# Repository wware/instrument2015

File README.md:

<!--
pip install markdown
python -m markdown README.md > README.html
-->

The Tooba is an electronic musical instrument built into a piece of PVC tubing (hence the name). It borrows principles from the Moog-style analog music synthesizers of past decades.

Way back when, one of my friends in high school was a guy named [Dave Wilson](http://www.matrixsynth.com/2010/08/rip-david-hillel-wilson-curator-of-new.html) whose father got him into 1970s-era Moog-style analog electronic music synthesizers. Dave created a museum of historical synthesizers in his home in Nashua, New Hampshire. Throughout our high school and college years, we exchanged ideas and circuits and bits of lore for various synthesizer hacks.

Music synthesizers of that era were actually special-purpose [analog computers](https://en.wikipedia.org/wiki/Analog_computer), performing arithmetic operations with [integrators, summers, and other such circuits](https://courses.engr.illinois.edu/ece486/labs/lab1/analog_computer_manual.pdf). These computations can be performed digitally by a microprocessor or special-purpose digital circuit (e.g. FPGA). So Dave and I both at various points and in various contexts wrote code to do that.

Sound generation in the Tooba (and keyboard scanning and voice assignment) is done in [C++](https://github.com/wware/instrument2015/blob/master/nextstage/teensy/teensy.ino) running on a 32-bit ARM microcontroller.

Newer stuff, November 2015
----

People have expressed interest in purchasing Toobas, so I have been planning some improvements.
* An internal [sound transducer](https://www.adafruit.com/products/1784) driven by a [D-class audio amp](http://www.ti.com/lit/ds/slos527a/slos527a.pdf).
* This requires a 12-volt battery, so I need a [5-volt regulator](https://www.adafruit.com/products/1385).
* A volume control, and jacks for both 1/4" (guitar amps) and 3.5mm (ear buds, computer speakers).
* Cleaned-up mechanics, no giant cabinet hinges.
* A lower-temperature process for soldering keys, so that the copper is not discolored. Producing keys is easier and quicker.

I've used this and another project to start planning 3D constructions in OpenSCAD. This can go farther. Write modules that produce OpenSCAD models for [inclusion in the whole](https://en.wikibooks.org/wiki/OpenSCAD_User_Manual/Include_Statement) but are also a [modular BOM](https://en.wikipedia.org/wiki/Bill_of_materials). Modules for 3D-printable blocks should be able to produce STL files and specify what materials are acceptable. Modules for parts from Home Depot or Adafruit or Digikey should include prices, SKUs, part numbers, etc.

Status, plans, etc
----

The first PVC prototype, the one shown at Providence on Aug 8th 2015, did all sound generation in the interrupt handler. More recently, the interrupt handler only transfers audio samples from a queue to the microcontroller's on-chip 12-bit DAC, and sound generation occurs in the loop() function.

* Doxygen stuff is now [online](http://wware.github.io/instrument2015/).
* Removing sound generation from the interrupt handler and moving it into the main loop solved a LOT of problems, and now I can run the interrupt at 40 kHz. But I am still hearing some aliasing, so I'll need a lowpass filter after the DAC. Use this [rail-to-rail op amp](http://www.digikey.com/product-detail/en/LT1677CN8%23PBF/LT1677CN8%23PBF-ND/962980).
* ADSR and other slow-moving things should perform real calculations at only around 50 Hz, not 40 or 50 kHz. In between calculations they should use linear interpolation. Four billion divided by 50K is 80K, so it’s fine to use 16 fraction bits to interpolate. This will significantly speed things up.
* Never copy or move blocks of data. Move pointers instead. The persistence data for a voice should live in one place and never move.
* The next step right now is to take the code in the Voice class and split it into VCO, VCA and ADSR classes. Then add a Noise class, a Scaler class, a Summer class, and a VCF class. The audio outputs of all these should be 24-bit signed integers in the range from -0x80_0000 to 0x7F_FFFF. Use asserts to make sure they never go outside that range.
* Set up a [monkey test framework](https://en.wikipedia.org/wiki/Monkey_test) that virtually pounds on the keyboard, and detects overflows, underruns, etc.
  * A [SWIG wrapper](http://swig.org/) will be very helpful with this.

Teensy 3.1 info
----

* [The Freescale Semiconductor web page](http://www.freescale.com/webapp/sps/site/prod_summary.jsp?code=K20_50) for the MK20DX256VLH7 processor used in the Teensy 3.1.
* [The datasheet](https://www.pjrc.com/teensy/K20P64M72SF1RM.pdf) that talks about GPIO programming starting on page 1331.
* [The Teensy 3.1 schematic](https://www.pjrc.com/teensy/schematic.html). PTB17 is the GPIO that I want to read. The Port B input register is at 0x400FF050. There is no MMU so no need for any mmap craziness.
* [Here](https://forum.pjrc.com/threads/25317-Assembly-coding-for-Teensy3-1) is a great discussion of embedding assembly in C code. Also see http://www.ethernut.de/en/documents/arm-inline-asm.html.
* [A C header file](http://www.keil.com/dd/docs/arm/freescale/kinetis/mk20d7.h) for registers in the MK20DX.
* [Some nice info](http://www.peter-cockerell.net/aalp/html/frames.html) on ARM assembly language.

Earlier prototype
----

I want to read the GPIO in assembly to accurately measure the period of the oscillator. This code ran on the June prototype and measured the capacitance of the touch sensitive keyboard. The capacitance was used in the RC time constant of a free-running oscillator and the idea here is to get a measurement roughly proportional to the period.

1. Set counter to zero.
2. If input is LOW, go to step 7.
3. Wait for a falling edge. Proceed when input is LOW.
4. Increment counter while waiting for rising edge. Proceed when input is HIGH.
5. Increment counter while waiting for falling edge. Proceed when input is LOW.
6. Go to step 10.
7. Wait for a rising edge. Proceed when input is HIGH.
8. Increment counter while waiting for falling edge. Proceed when input is LOW.
9. Increment counter while waiting for rising edge. Proceed when input is HIGH.
10. Return counter.

So that piece is assembly, and then in C you choose a touch contact and call that function. That should ensure that you read the keyboard about as fast as it can be read. The code for this is buried in [the sandbox directory](https://github.com/wware/instrument2015/blob/master/sandbox/prototype1/prototype1.ino#L7).

~~~
static int measurePeriod(void)
{
    // Step 1, set up registers
    int count = 0, x = 0, mask = 1 << 17, addr = 0x400ff050;
#   define READ_INPUT  "ldr %1, [%3]\n"     "ands %1, %1, %2\n"
#   define INC_COUNT   "add %0, %0, #1\n"
    asm volatile(
        // Step 2, if input is low go to step 7
        READ_INPUT
        "beq step7"                             "\n"
        // Step 3, wait for falling edge
        "step3:"                                "\n"

        ... lots more code ...

        "step10:"                               "\n"
        : "+r" (count), "+r" (x), "+r" (mask), "+r" (addr)
    );
    return count;
}
~~~

This works well in both the [Arduino/Teensy IDE](https://www.pjrc.com/teensy/teensyduino.html) and in the [online ARM C++ compiler](http://assembly.ynh.io/).

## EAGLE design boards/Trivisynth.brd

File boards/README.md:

Printed circuit boards
====

I use Cadsoft Eagle for PCB layout. For these designs you'll need to pick up
some third-party libraries.

* [Teensy 3.0 library](https://forum.pjrc.com/attachment.php?attachmentid=184&d=1358973338)
  - [Discussion of Teensy library](https://www.pjrc.com/teensy/eagle_lib.html)
* [Sparkfun Connector library](https://github.com/sparkfun/SparkFun-Eagle-Libraries)

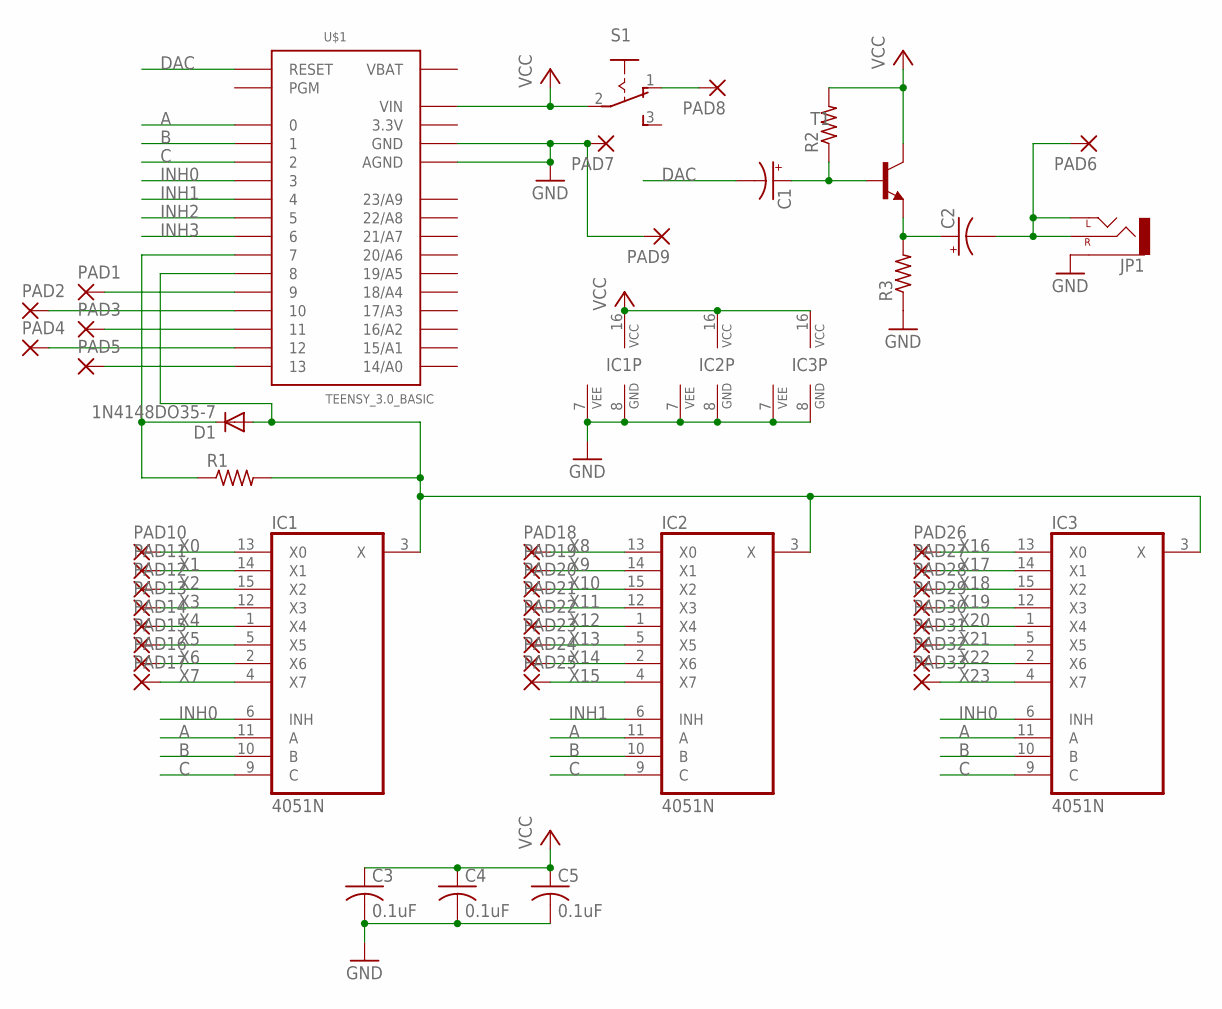
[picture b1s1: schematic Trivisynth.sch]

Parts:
C1, C2: CPOL-USE2-5; E2-5
C3, C4, C5: 0.1uF; C025-025X050
D1: 1N4148DO35-7; DO35-7
IC1, IC2, IC3: 4051N; DIL16
JP1: AUDIO-JACKPTH; AUDIO-JACK
PAD1, PAD2, PAD3, PAD4, PAD5, PAD6, PAD7, PAD8, PAD9, PAD10, PAD11, PAD12, PAD13, PAD14, PAD15, PAD16, PAD17, PAD18, PAD19, PAD20, PAD21, PAD22, PAD23, PAD24, PAD25, PAD26, PAD27, PAD28, PAD29, PAD30, PAD31, PAD32, PAD33: 2,15/1,0
R1, R2, R3: R-US_0207/10; 0207/10
S1: 255SB
T1: -NPN-TO92-EBC; TO92-EBC
U$1: TEENSY_3.0_BASIC

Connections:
3.3V: U$1.3.3V, U$1.3.3V1 (3.3V)
A: IC1.11 (A), IC2.11 (A), IC3.11 (A), U$1.0
B: IC1.10 (B), IC2.10 (B), IC3.10 (B), U$1.1
C: IC1.9 (C), IC2.9 (C), IC3.9 (C), U$1.2
DAC: C1.-, U$1.RESET
GND: C3.2, C4.2, C5.2, IC1.7 (VEE), IC1.8 (GND), IC2.7 (VEE), IC2.8 (GND), IC3.7 (VEE), IC3.8 (GND), JP1.SLEEVE, PAD7.1, PAD9.1, R3.1, U$1.AGND, U$1.GND, U$1.GND1 (GND)
INH0: IC1.6 (INH), IC3.6 (INH), U$1.3
INH1: IC2.6 (INH), U$1.4
INH2: U$1.5
INH3: U$1.6
unnamed: PAD8.1, S1.1 (O)
unnamed: D1.A, IC1.3 (X), IC2.3 (X), IC3.3 (X), R1.2, U$1.8
unnamed: C1.+, R2.1, T1.B
unnamed: C2.+, R3.2, T1.E
unnamed: D1.C, R1.1, U$1.7
unnamed: C2.-, JP1.RING (RIGHT), JP1.TIP (LEFT), PAD6.1
unnamed: PAD1.1, U$1.9
unnamed: PAD2.1, U$1.10
unnamed: PAD3.1, U$1.11
unnamed: PAD4.1, U$1.12
unnamed: PAD5.1, U$1.13
VBAT: U$1.VBAT
VCC: C3.1, C4.1, C5.1, IC1.16 (VCC), IC2.16 (VCC), IC3.16 (VCC), R2.2, S1.2, T1.C, U$1.VIN
X0: IC1.13 (X0), PAD10.1
X1: IC1.14 (X1), PAD11.1
X2: IC1.15 (X2), PAD12.1
X3: IC1.12 (X3), PAD13.1
X4: IC1.1 (X4), PAD14.1
X5: IC1.5 (X5), PAD15.1
X6: IC1.2 (X6), PAD16.1
X7: IC1.4 (X7), PAD17.1
X8: IC2.13 (X0), PAD18.1
X9: IC2.14 (X1), PAD19.1
X10: IC2.15 (X2), PAD20.1
X11: IC2.12 (X3), PAD21.1
X12: IC2.1 (X4), PAD22.1
X13: IC2.5 (X5), PAD23.1
X14: IC2.2 (X6), PAD24.1
X15: IC2.4 (X7), PAD25.1
X16: IC3.13 (X0), PAD26.1
X17: IC3.14 (X1), PAD27.1
X18: IC3.15 (X2), PAD28.1
X19: IC3.12 (X3), PAD29.1
X20: IC3.1 (X4), PAD30.1
X21: IC3.5 (X5), PAD31.1
X22: IC3.2 (X6), PAD32.1
X23: IC3.4 (X7), PAD33.1

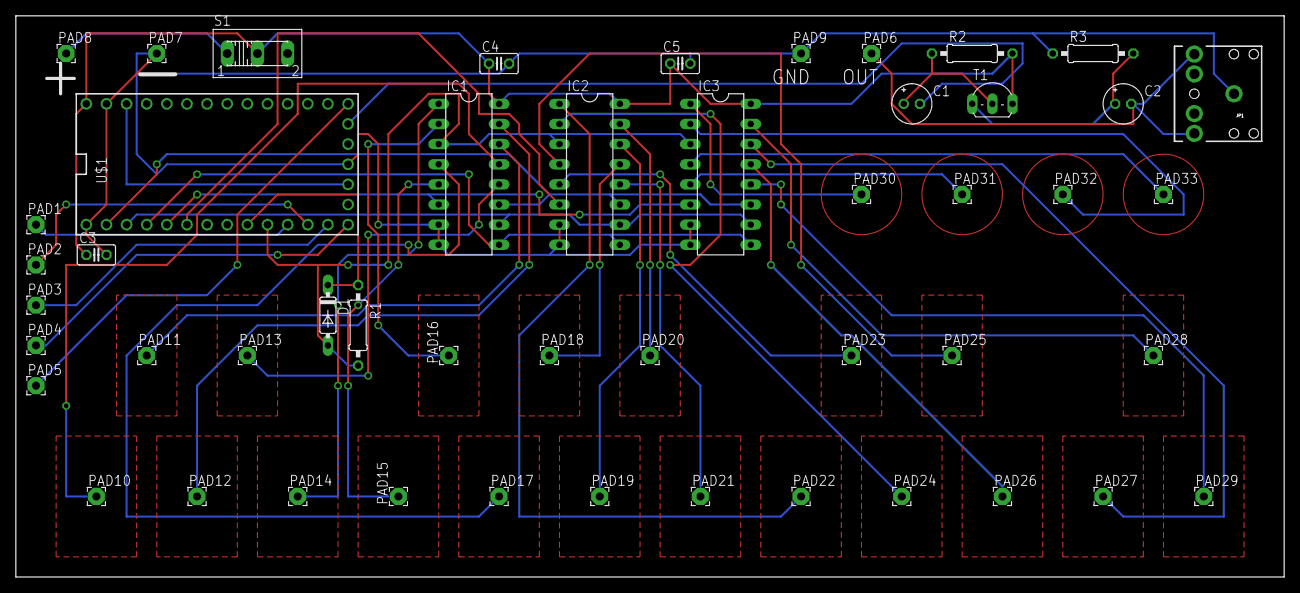
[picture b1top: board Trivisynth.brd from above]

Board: 2 copper layers, 160.0 x 70.8 mm, 49 parts (0 on the bottom side), 44 nets.

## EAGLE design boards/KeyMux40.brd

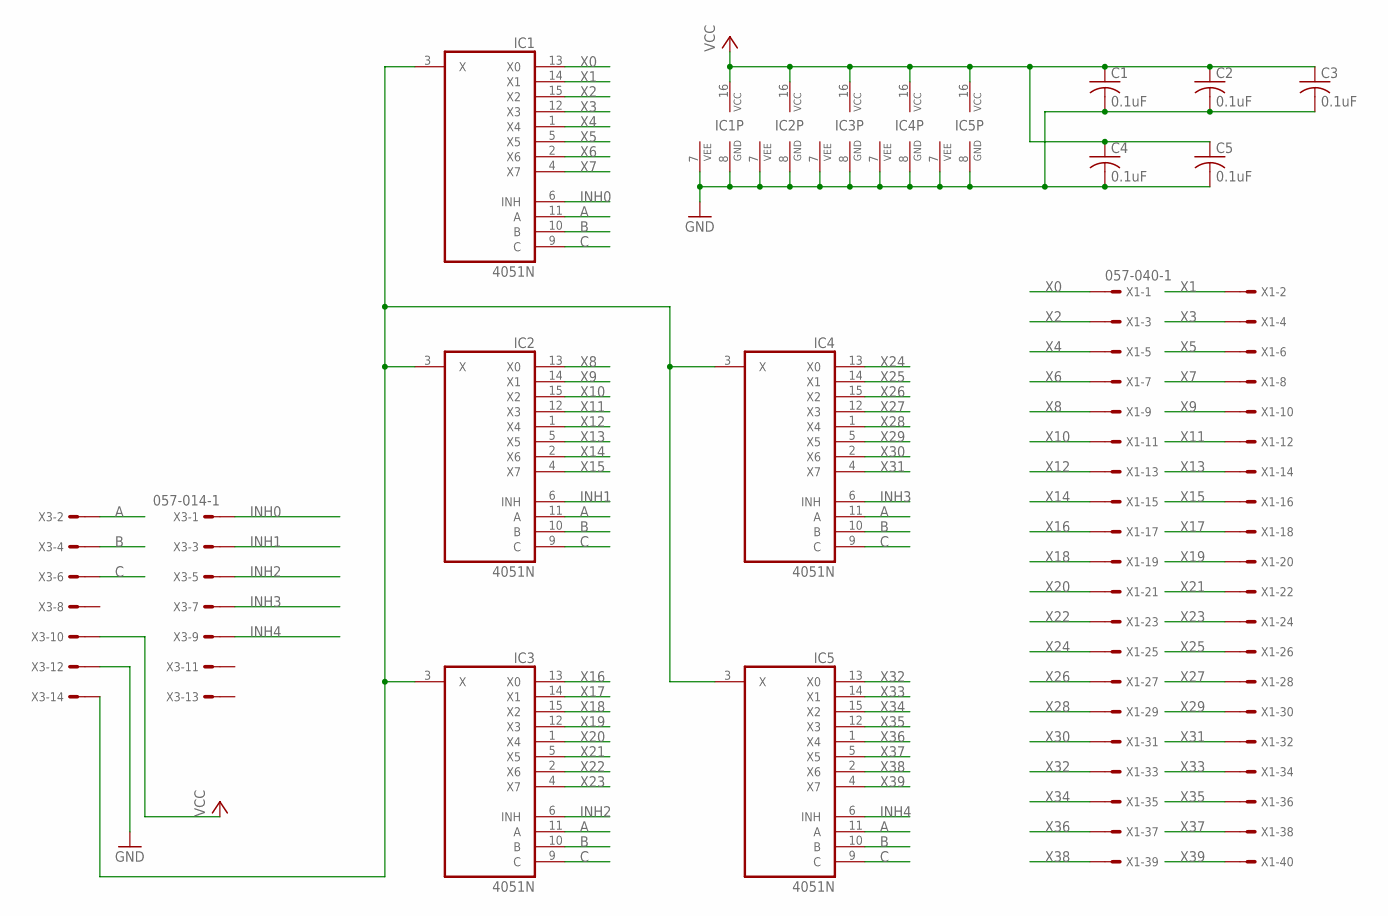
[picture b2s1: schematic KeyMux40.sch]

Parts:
C1, C2, C3, C4, C5: 0.1uF; C025-025X050
IC1, IC2, IC3, IC4, IC5: 4051N; DIL16
X1: 057-040-1
X3: 057-014-1

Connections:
A: IC1.11 (A), IC2.11 (A), IC3.11 (A), IC4.11 (A), IC5.11 (A), X3.2
B: IC1.10 (B), IC2.10 (B), IC3.10 (B), IC4.10 (B), IC5.10 (B), X3.4
C: IC1.9 (C), IC2.9 (C), IC3.9 (C), IC4.9 (C), IC5.9 (C), X3.6
GND: C1.2, C2.2, C3.2, C4.2, C5.2, IC1.7 (VEE), IC1.8 (GND), IC2.7 (VEE), IC2.8 (GND), IC3.7 (VEE), IC3.8 (GND), IC4.7 (VEE), IC4.8 (GND), IC5.7 (VEE), IC5.8 (GND), X3.12
INH0: IC1.6 (INH), X3.1
INH1: IC2.6 (INH), X3.3
INH2: IC3.6 (INH), X3.5
INH3: IC4.6 (INH), X3.7
INH4: IC5.6 (INH), X3.9
unnamed: IC1.3 (X), IC2.3 (X), IC3.3 (X), IC4.3 (X), IC5.3 (X), X3.14
VCC: C1.1, C2.1, C3.1, C4.1, C5.1, IC1.16 (VCC), IC2.16 (VCC), IC3.16 (VCC), IC4.16 (VCC), IC5.16 (VCC), X3.10
X0: IC1.13 (X0), X1.1
X1: IC1.14 (X1), X1.2
X2: IC1.15 (X2), X1.3
X3: IC1.12 (X3), X1.4
X4: IC1.1 (X4), X1.5
X5: IC1.5 (X5), X1.6
X6: IC1.2 (X6), X1.7
X7: IC1.4 (X7), X1.8
X8: IC2.13 (X0), X1.9
X9: IC2.14 (X1), X1.10
X10: IC2.15 (X2), X1.11
X11: IC2.12 (X3), X1.12
X12: IC2.1 (X4), X1.13
X13: IC2.5 (X5), X1.14
X14: IC2.2 (X6), X1.15
X15: IC2.4 (X7), X1.16
X16: IC3.13 (X0), X1.17
X17: IC3.14 (X1), X1.18
X18: IC3.15 (X2), X1.19
X19: IC3.12 (X3), X1.20
X20: IC3.1 (X4), X1.21
X21: IC3.5 (X5), X1.22
X22: IC3.2 (X6), X1.23
X23: IC3.4 (X7), X1.24
X24: IC4.13 (X0), X1.25
X25: IC4.14 (X1), X1.26
X26: IC4.15 (X2), X1.27
X27: IC4.12 (X3), X1.28
X28: IC4.1 (X4), X1.29
X29: IC4.5 (X5), X1.30
X30: IC4.2 (X6), X1.31
X31: IC4.4 (X7), X1.32
X32: IC5.13 (X0), X1.33
X33: IC5.14 (X1), X1.34
X34: IC5.15 (X2), X1.35
X35: IC5.12 (X3), X1.36
X36: IC5.1 (X4), X1.37
X37: IC5.5 (X5), X1.38
X38: IC5.2 (X6), X1.39
X39: IC5.4 (X7), X1.40

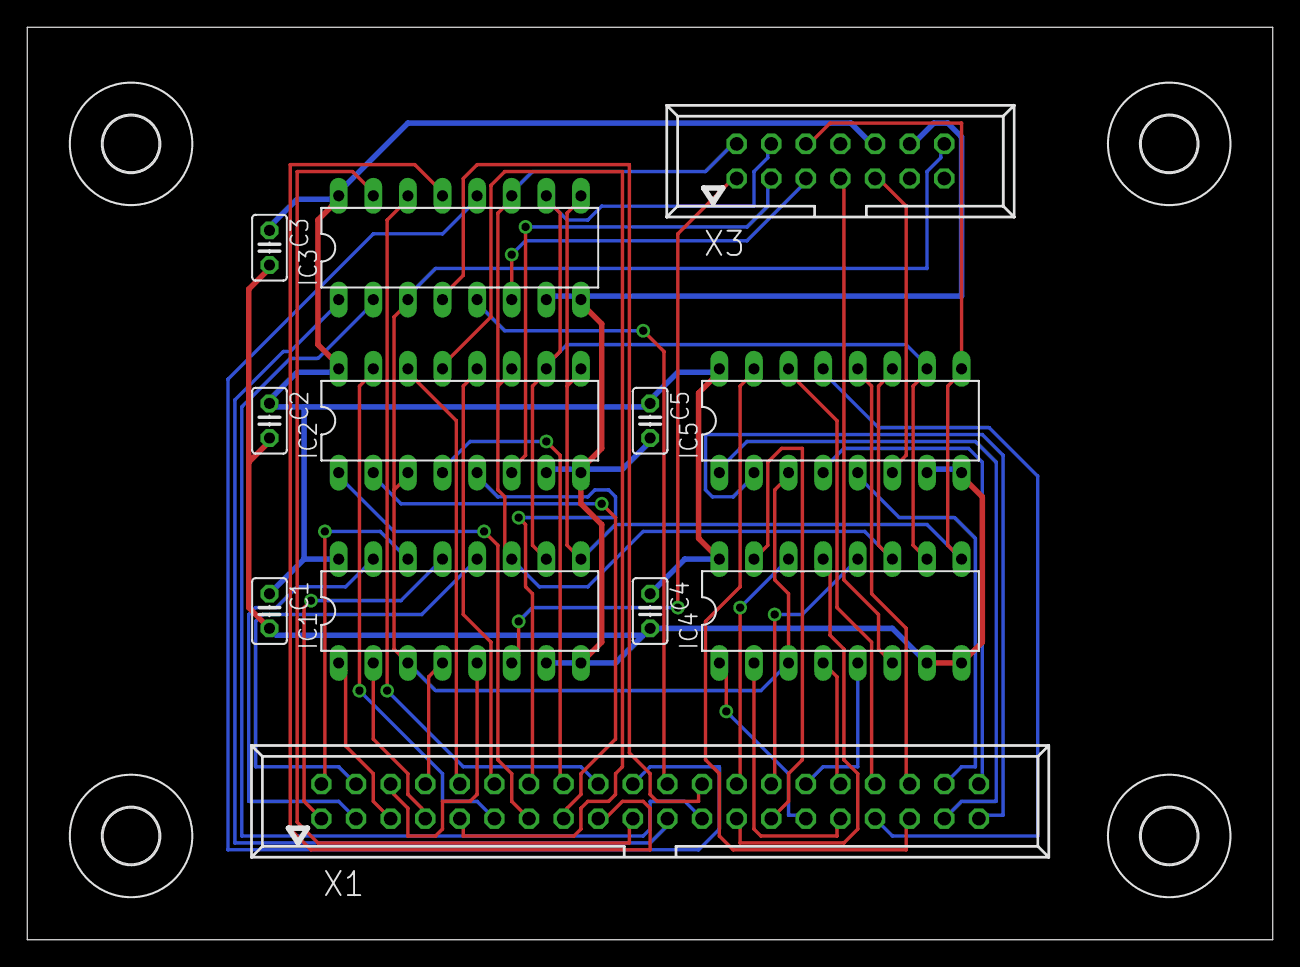
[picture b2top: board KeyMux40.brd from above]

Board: 2 copper layers, 91.4 x 67.0 mm, 16 parts (0 on the bottom side), 51 nets.

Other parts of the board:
U$1, U$2, U$3, U$4: 4,1

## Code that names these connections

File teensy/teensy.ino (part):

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    CELLO, CHOIR_AAHS, TRUMPET, FLUTE
};

#define INH0  2
#define INH1  14
#define INH2  7
#define INH3  8
#define INH4  6

uint32_t inhibits[] = {INH0, INH1, INH2, INH3, INH4};

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
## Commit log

2015-07-19 Initial commit, empty README.md
2015-07-26 Initial prototype, RPi as sound generator
2015-07-27 Scrap the RPi, run everything on the Teensy
2015-07-27 Set up sandbox, hack interrupt handlers, ARM assembly
2015-07-30 Arduino compiler warning nitpick
2015-07-30 multiple voices
2015-07-30 exponential attack
2015-08-08 Use correct constant for attack exponential
2015-08-08 hexagon pattern
2015-08-08 Discrete time 2nd order filter without z transforms
2015-08-08 lower sampling frequency, more voices
2015-08-08 Hardware debug, assembly language, GPIOs, etc
2015-08-08 Scanning keys up to E-flat
2015-08-10 Include description and Youtube video in README.
2015-08-12 a bunch of refactoring
2015-08-13 add the queue stuff
2015-08-13 Gnuplot, OSX adaptations, bug fixes
2015-08-13 wire up the queue
2015-08-14 Bug fixes and improvements.
2015-08-14 Better documentation for Queue class
2015-08-14 Remove a deprecated file.
2015-08-14 Start writing Doxygen comments for the code.
2015-08-14 More doxygen hacking
2015-08-14 Add a status/todo list to README.md
2015-08-14 A SWIG wrapper for the C++ code
2015-08-14 Accommodate both Linux and OSX
2015-08-14 Doxygen stuff
2015-08-14 Pointer to Doxygen stuff (gh-pages)
2015-08-15 Move sampling rate to 40 kHz
2015-08-16 Modules, more SWIG, chorusing
2015-08-16 move modules into synth.h
2015-08-17 better oscillator outputs
2015-08-17 tweak parameters empirically
2015-08-17 more interesting voice
2015-08-17 filter with integer arithmetic, kinda rough
2015-08-17 more filter analysis in python
2015-08-18 More efficient Oscillator and ADSR.
2015-08-18 mess around with oscillators
2015-08-18 tinker with filter datapaths, fix a small bug
2015-08-19 Valgrind for profiling
2015-08-20 correct my WORST IDEA EVER
2015-08-20 how big are these numbers?
2015-08-20 filter is REALLY int math now
2015-08-20 use new filter
2015-08-20 A class to help with profiling code
2015-08-20 better testing on the Mac
2015-08-20 a little more work on clipping
2015-08-20 Back down the sampling rate a bit.
2015-08-20 Beginnings of a toolchain build script.
2015-08-20 update the swig test
2015-08-20 bump up hysteresis, fix filter damping issue
2015-08-20 scrap NUM_VOICE_BITS
2015-08-20 Improved assertions, and sound on ubuntu
2015-08-22 Reorganize, refactor, clean up.
2015-08-22 works on the trivisynth
2015-08-22 code simplifications
2015-08-22 pick up an ABC parser
2015-08-22 work on readme for trivisynth stuff
2015-08-22 fix title in Doxyfile
2015-08-24 import stuff from Synth.cpp repo
2015-08-28 fixed some wiring errors
2015-08-29 Use stuff from Synth.cpp repository for sound generation.
2015-09-04 threaded rod holder
2015-09-21 bump Synth.cpp
2015-09-24 bigger keyboard, ready for Maker Faire NYC
2015-09-24 octave transpose
2015-09-27 slightly better
2015-09-30 symbolic links >>> copying files
2015-09-30 autocalibration working
2015-09-30 fine points
2015-10-01 PCB stuff
2015-10-02 fix an autocalibration bug
2015-10-07 trivial fixes
2015-10-25 Measurements, and bug fixes
2015-10-25 Control 4051s with assembly language.
2015-10-25 Start work on board for second instrument.
2015-10-25 touch-sensitive trivisynth
2015-11-12 start 3d plan
2015-11-12 try yaml
2015-11-12 tinkering
2015-11-27 Rename schematic, add an image and a BRD file.
2016-07-24 more yaml work
2016-09-11 Begin work on Megachordotron
2016-09-12 Further work.
2016-09-13 Restart a note if its pitch changes.
2016-09-13 Try to fix the timing bug.
2016-09-18 Improvements to startup script.
2016-09-18 Better chord choices
2016-09-20 ifdef wrapper for header file
2016-09-20 Try organizing state better.
2016-09-20 yet more
2016-09-22 Two new classes.
2021-03-06 Cadsoft Eagle files for 4051 board
2021-03-06 and an image file

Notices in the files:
parts and their libraries:
SparkFun-Connectors: Licensing: Creative Commons ShareAlike 4.0 International - https://creativecommons.org/licenses/by-sa/4.0
